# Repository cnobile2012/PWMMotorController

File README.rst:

***************************************
Voltage-Controlled PWM Motor Controller
***************************************
The MIT License (MIT)

**Don't use this board and schematic I've developed a much better and more stable one click below.** 
`VoltageControlledPWM <https://github.com/cnobile2012/VoltageControlledPWM>`_

=======
LTspice
=======

Spice files for testing the circuit viability.

=====
KiCAD
=====

KiCAD files of the schematic and PCB.

Feel free to contact me at: carl dot nobile at gmail.com

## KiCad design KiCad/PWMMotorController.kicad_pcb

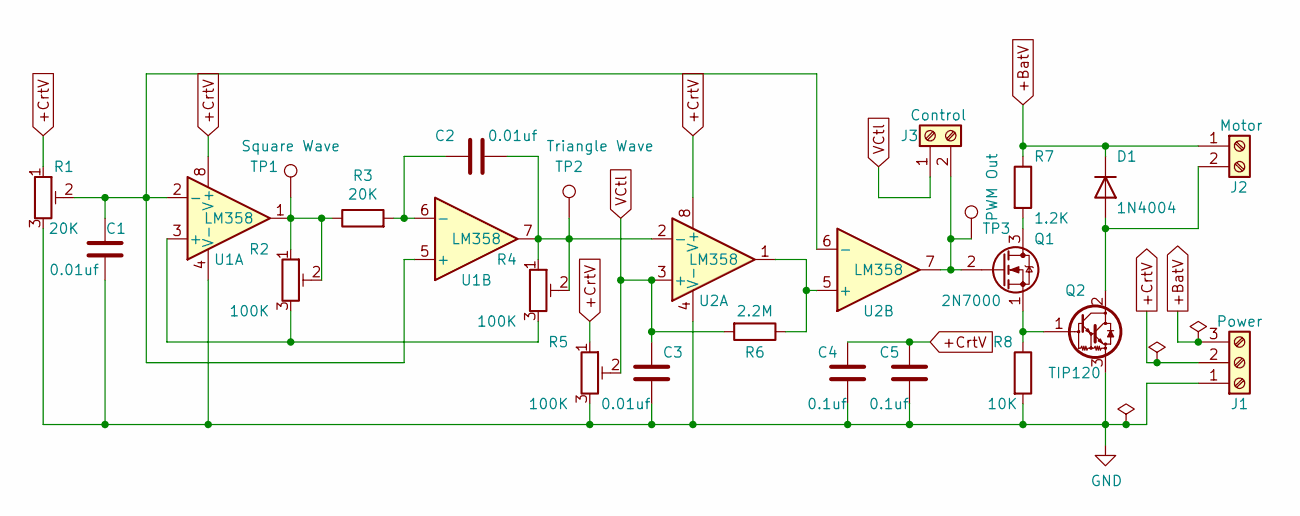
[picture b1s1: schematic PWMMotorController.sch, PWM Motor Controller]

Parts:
C1, C2, C3: 0.01uf; C_Disc_D3.4mm_W2.1mm_P2.50mm
C4, C5: 0.1uf; C_Disc_D3.4mm_W2.1mm_P2.50mm
D1: 1N4004; D_DO-41_SOD81_P10.16mm_Horizontal
J1: Power; TerminalBlock_MetzConnect_Type094_RT03503HBLU_1x03_P5.00mm_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
J2: Motor; TerminalBlock_MetzConnect_Type094_RT03502HBLU_1x02_P5.00mm_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
J3: Control; TerminalBlock_MetzConnect_Type094_RT03502HBLU_1x02_P5.00mm_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
Q1: 2N7000; TO-92_Inline
Q2: TIP120; TO-220-3_Horizontal_TabDown
R1: 20K; Potentiometer_Bourns_3299P_Horizontal
R2, R4, R5: 100K; Potentiometer_Bourns_3299P_Horizontal
R3: 20K; R_Axial_DIN0204_L3.6mm_D1.6mm_P7.62mm_Horizontal
R6: 2.2M; R_Axial_DIN0204_L3.6mm_D1.6mm_P7.62mm_Horizontal
R7: 1.2K; R_Axial_DIN0204_L3.6mm_D1.6mm_P7.62mm_Horizontal
R8: 10K; R_Axial_DIN0204_L3.6mm_D1.6mm_P7.62mm_Horizontal
TP1: Square Wave; TestPoint_Loop_D2.50mm_Drill1.0mm_LowProfile
TP2: Triangle Wave; TestPoint_Loop_D2.50mm_Drill1.0mm_LowProfile
TP3: PWM Out; TestPoint_Loop_D2.50mm_Drill1.0mm_LowProfile
U1, U2: LM358; DIP-8_W7.62mm

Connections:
+BatV: D1.1 (K), J1.3, J2.1, R7.1
+CrtV: C4.1, C5.1, J1.2, R1.1, R5.1, U1.8 (V+), U2.8 (V+)
GND: C1.2, C3.2, C4.2, C5.2, J1.1, Q2.3 (E), R1.3, R5.3, R8.2, U1.4 (V-), U2.4 (V-)
unnamed: C1.1, R1.2, U1.2 (-), U1.5 (+), U2.6 (-)
unnamed: C2.1, R3.2, U1.6 (-)
unnamed: C2.2, R4.1, R4.2, TP2.1, U1.7, U2.2 (-)
unnamed: D1.2 (A), J2.2, Q2.2 (C)
unnamed: J3.2, Q1.2 (G), TP3.1, U2.7
unnamed: Q1.1 (S), Q2.1 (B), R8.1
unnamed: Q1.3 (D), R7.2
unnamed: R2.1, R2.2, R3.1, TP1.1, U1.1
unnamed: R2.3, R4.3, U1.3 (+)
unnamed: R6.1, U2.1, U2.5 (+)
VCtl: C3.1, J3.1, R5.2, R6.2, U2.3 (+)

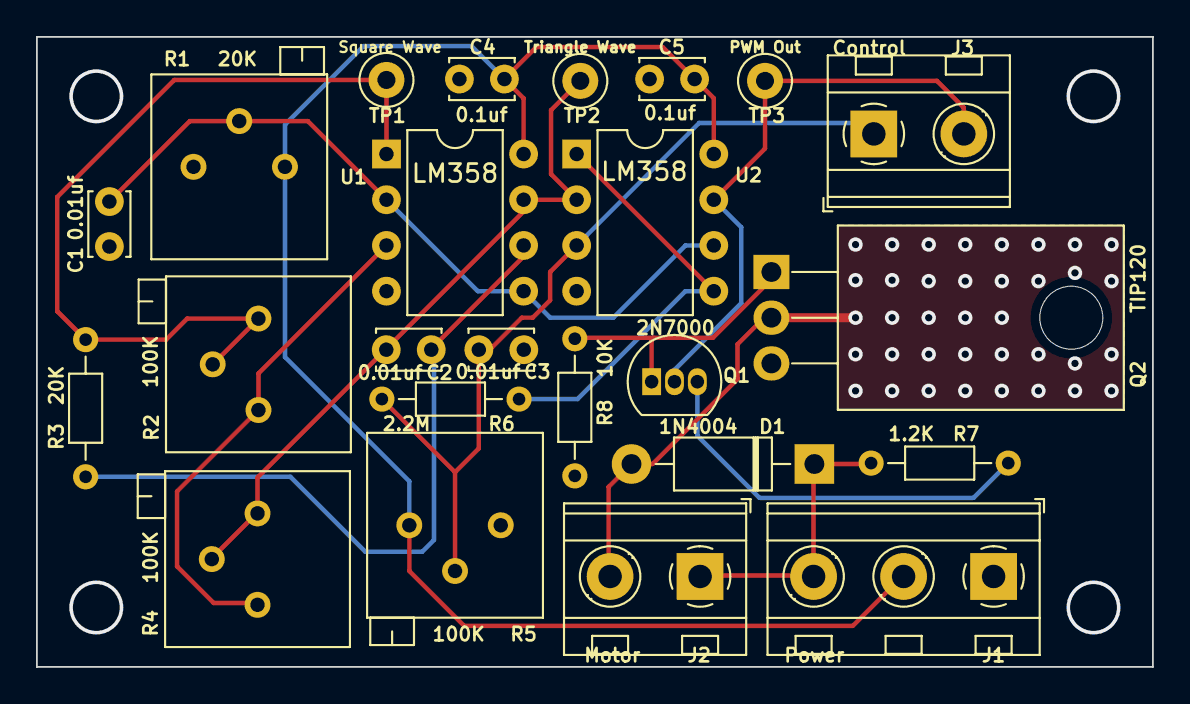
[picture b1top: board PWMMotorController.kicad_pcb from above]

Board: 2 copper layers, 62.0 x 35.0 mm, 24 parts (0 on the bottom side), 14 nets.

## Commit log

2020-12-21 Initial commit.
2020-12-21 Changed some wording.
2021-01-16 Added a new diagram for testing the voltage control.
2021-01-16 Minor changes to the circuits.
2021-03-19 Updated Make file to clean more files.
2021-03-19 Renamed all *.asc files and made a few minor updates
2021-03-19 Did some more renaming.
2021-07-21 Recommendation to use other repo.
2021-07-21 Update READEME.rst
    Hopefully, I fixed the link this time.
2021-07-21 Update README.rst
    Yet again.
2021-07-21 Update README.rts
    Once again.
